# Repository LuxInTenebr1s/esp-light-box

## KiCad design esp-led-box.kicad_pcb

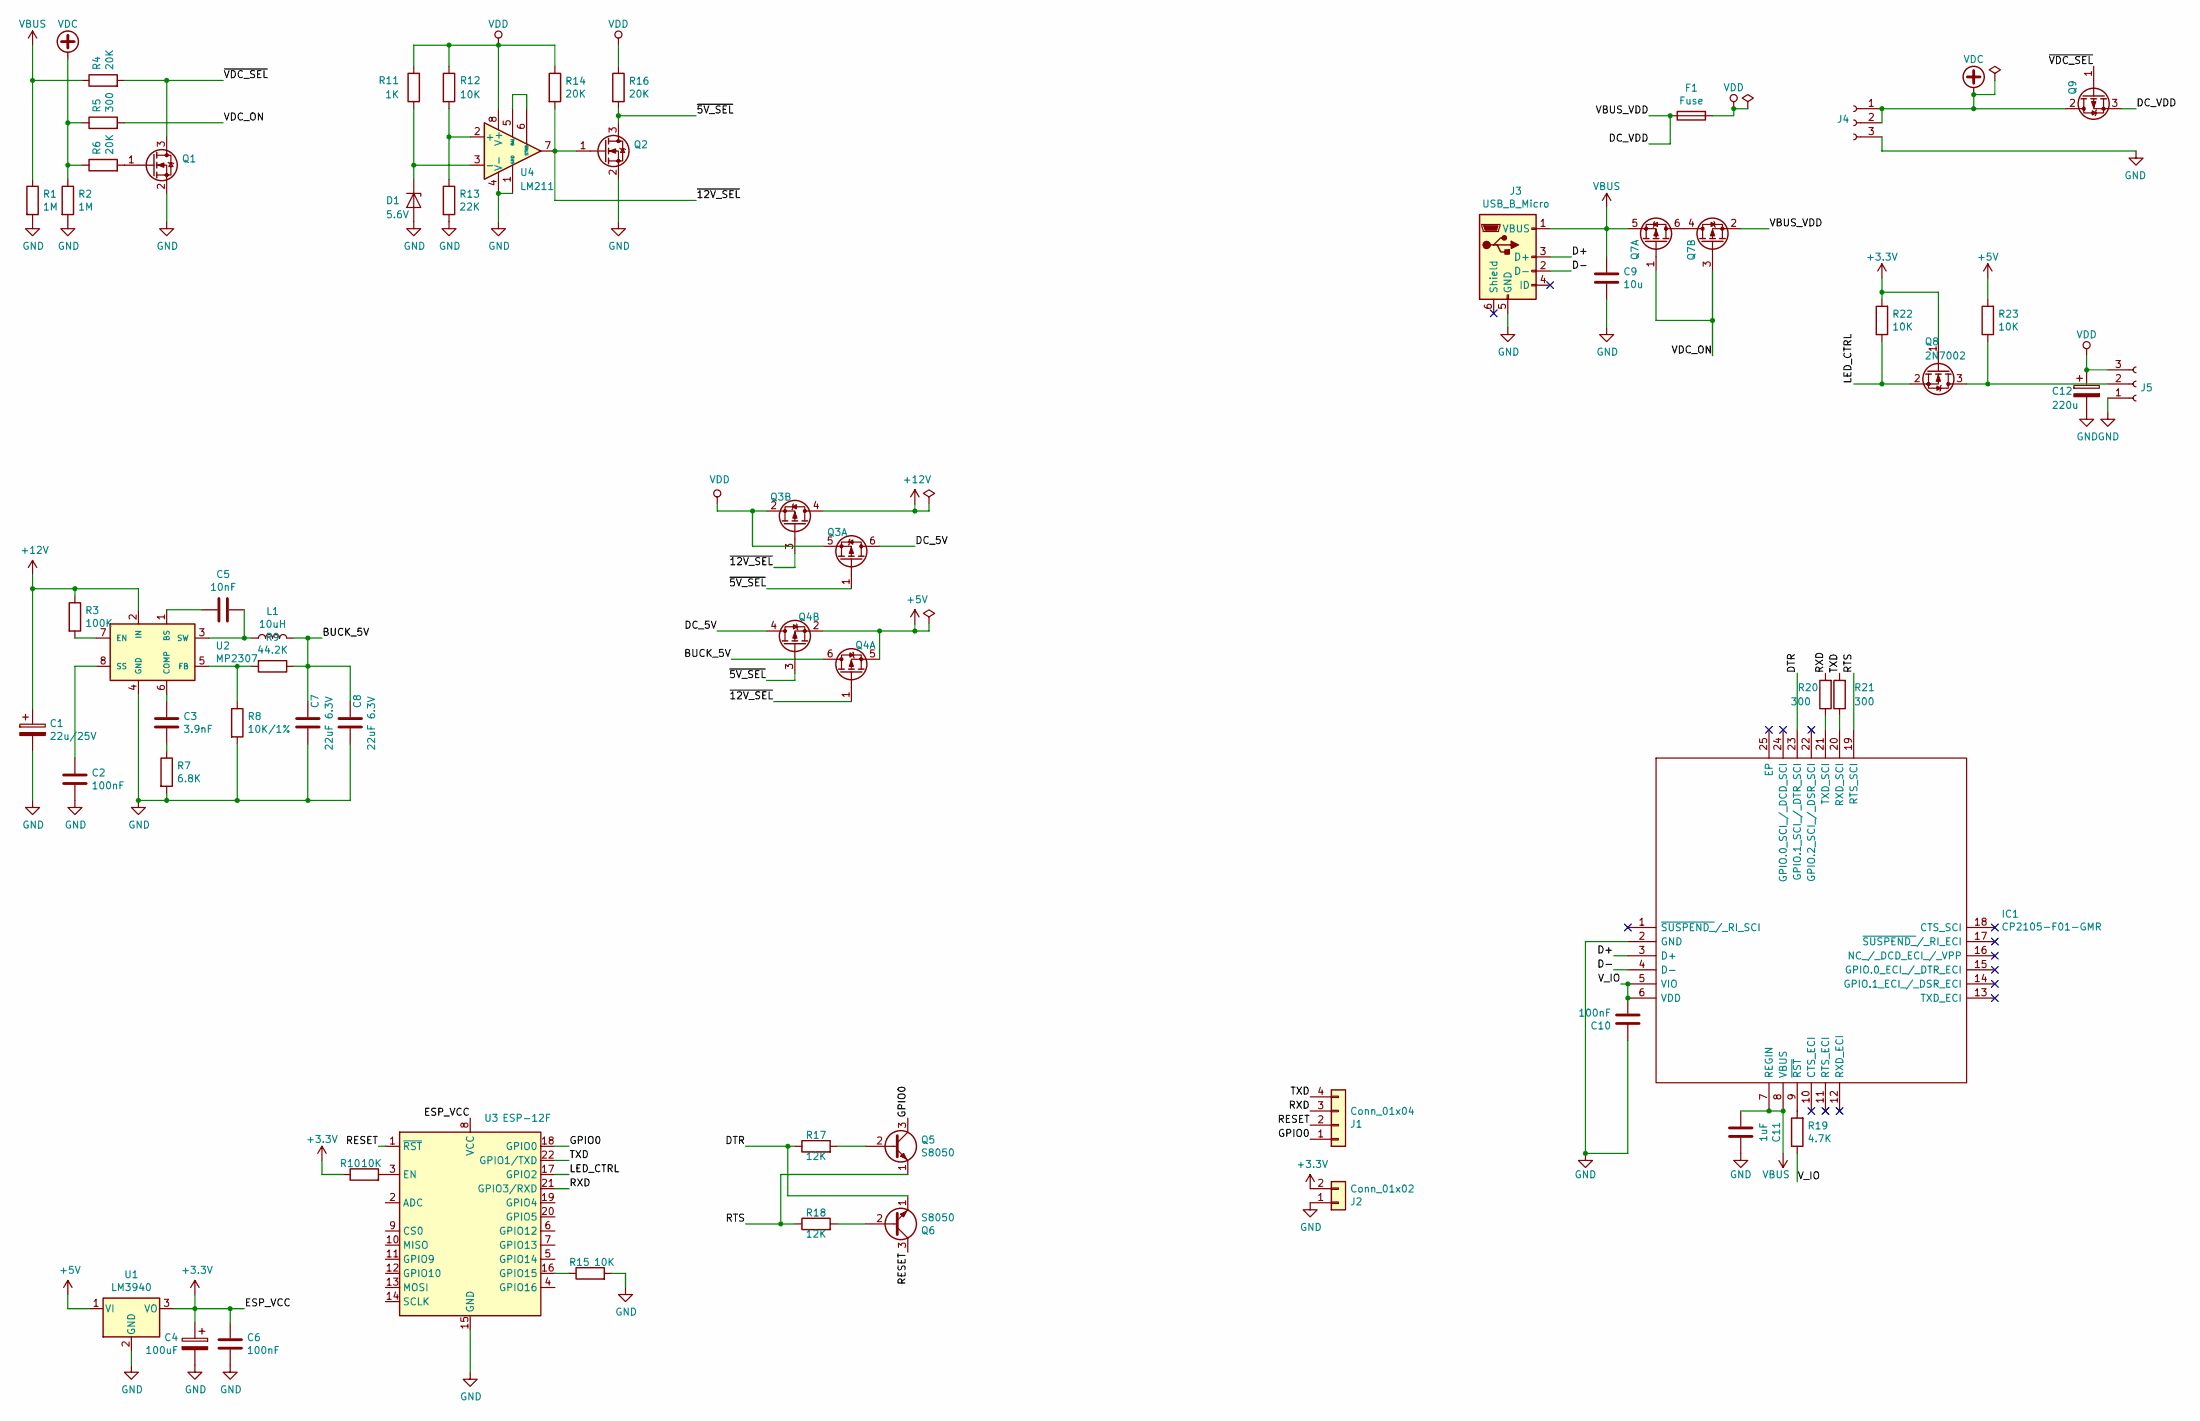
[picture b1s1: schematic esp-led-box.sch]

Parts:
C1: 22u/25V; C_0805_2012Metric; LCSC C45783
C2, C6, C10: 100nF; C_0402_1005Metric; LCSC C307331
C3: 3.9nF; C_0402_1005Metric; LCSC C18047
C4: 100uF; CP_EIA-3528-21_Kemet-B; LCSC C16133
C5: 10nF; C_0402_1005Metric; LCSC C15195
C7, C8: 22uF 6.3V; C_0603_1608Metric; LCSC C59461
C9: 10u; C_0603_1608Metric; LCSC C19702
C11: 1uF; C_0402_1005Metric
C12: 220u; CP_Elec_6.3x7.7; LCSC C127327
D1: 5.6V; D_MiniMELF; LCSC C8062
F1: Fuse; fuseholder_blade_common_aliexpress
IC1: CP2105-F01-GMR; QFN50P400X400X80-25N-D; Manufacturer_Part_Number CP2105-F01-GMR; Mouser Part Number 634-CP2105-F01-GMR
J1: Conn_01x04; PinHeader_1x04_P2.54mm_Vertical
J2: Conn_01x02; PinHeader_1x02_P2.54mm_Vertical
J3: USB_B_Micro; USB_Micro-B_Molex-105017-0001
J4, J5: Conn_01x03_Female; SolderWire_1x03_2.5x6
L1: 10uH; L_Sunlord_MWSA0518_5.4x5.2mm; LCSC C181721
Q1, Q2, Q8: 2N7002; SOT-23; LCSC C8545
Q3, Q4, Q7: Q_PMOS_DGS; SOT-23-6; LCSC C148368
Q5, Q6: S8050; SOT-23; LCSC C2146
Q9: Q_PMOS_DGS; TO-252-2; LCSC C67281
R1, R2: 1M; R_0402_1005Metric; LCSC C26083
R3: 100K; R_0402_1005Metric; LCSC C25741
R4, R6: 20K; R_0603_1608Metric; LCSC C4184
R5: 300; R_0805_2012Metric; LCSC C17617
R7: 6.8K; R_0402_1005Metric; LCSC C25917
R8: 10K/1%; R_0402_1005Metric; LCSC C25744
R9: 44.2K; R_0402_1005Metric; LCSC C25895
R10, R12, R15, R22, R23: 10K; R_0402_1005Metric; LCSC C25744
R11: 1K; R_0603_1608Metric; LCSC C21190
R13: 22K; R_0402_1005Metric; LCSC C25768
R14, R16: 20K; R_0402_1005Metric; LCSC C25765
R17, R18: 12K; R_0402_1005Metric; LCSC C25752
R19: 4.7K; R_0402_1005Metric; LCSC C25900
R20, R21: 300; R_0402_1005Metric; LCSC C25774
U1: LM3940; SOT-223-3_TabPin2; LCSC C140319
U2: MP2307; SOIC-8_3.9x4.9mm_P1.27mm; LCSC C18921
U3: ESP-12F; ESP-12E
U4: LM211; SOIC-8-1EP_3.9x4.9mm_P1.27mm_EP2.29x3mm; LCSC C99580

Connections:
+3V3: C4.1, C6.1, J2.2, Q8.1 (G), R10.1, R22.2, U1.3 (VO), U3.8 (VCC)
+5V: Q4.2 (S), Q4.5 (S), R23.2, U1.1 (VI)
+12V: C1.1, Q3.4 (D), R3.1, U2.2 (IN)
/BUCK_5V: C7.1, C8.1, L1.2, Q4.6 (D), R9.1
/D+: IC1.3 (D+), J3.3 (D+)
/D-: IC1.4 (D-), J3.2 (D-)
/DC_5V: Q3.6 (D), Q4.4 (D)
/DC_VDD: F1.1, Q7.2 (S), Q9.3 (S)
/DTR: IC1.23 (GPIO.1_SCI_/_DTR_SCI), Q6.1 (E), R17.1
/GPIO0: J1.1, Q5.3 (C), U3.18 (GPIO0)
/LED_CTRL: Q8.2 (S), R22.1, U3.17 (GPIO2)
/RESET: J1.2, Q6.3 (C), U3.1 (~RST)
/RTS: IC1.19 (RTS_SCI), Q5.1 (E), R18.1
/RXD: J1.3, R20.2, U3.21 (GPIO3/RXD)
/TXD: J1.4, R21.2, U3.22 (GPIO1/TXD)
/VDC_ON: Q7.1 (G), Q7.3 (G), R5.2
/V_IO: C10.2, IC1.5 (VIO), IC1.6 (VDD), R19.1
/~5V_SEL: Q2.3 (D), Q3.1 (G), Q4.3 (G), R16.2; also elsewhere on the board
/~12V_SEL: Q2.1 (G), Q3.3 (G), Q4.1 (G), R14.2, U4.7; also elsewhere on the board
/~VDC_SEL: Q1.3 (D), Q9.1 (G), R4.2
GND: C1.2, C2.2, C4.2, C6.2, C7.2, C8.2, C9.1, C10.1, C11.2, C12.2, D1.2 (A), IC1.2 (GND), J2.1, J3.5 (GND), J4.3, J5.1, Q1.2 (S), Q2.2 (S), R1.2, R2.2, R7.2, R8.2, R13.2, R15.2, U1.2 (GND), U2.4 (GND), U3.15 (GND), U4.1 (GND), U4.4 (V-); also elsewhere on the board
unnamed: C2.1, U2.8 (SS)
unnamed: C3.1, U2.6 (COMP)
unnamed: C3.2, R7.1
unnamed: C5.1, L1.1, U2.3 (SW)
unnamed: C5.2, U2.1 (BS)
unnamed: D1.1 (K), R11.1, U4.3 (-)
unnamed: IC1.9 (~RST), R19.2
unnamed: IC1.20 (RXD_SCI), R21.1
unnamed: IC1.21 (TXD_SCI), R20.1
unnamed: J5.2, Q8.3 (D), R23.1
unnamed: Q1.1 (G), R6.2
unnamed: Q5.2 (B), R17.2
unnamed: Q6.2 (B), R18.2
unnamed: Q7.4 (D), Q7.6 (D)
unnamed: R3.2, U2.7 (EN)
unnamed: R8.1, R9.2, U2.5 (FB)
unnamed: R10.2, U3.3 (EN)
unnamed: R12.2, R13.1, U4.2 (+)
unnamed: R15.1, U3.16 (GPIO15)
unnamed: U4.5 (BAL), U4.6 (STRB)
VBUS: C9.2, C11.1, IC1.7 (REGIN), IC1.8 (VBUS), J3.1 (VBUS), Q7.5 (S), R1.1, R4.1
VDC: J4.1, J4.2, Q9.2 (D), R2.1, R5.1, R6.1
VDD: C12.1, F1.2, J5.3, Q3.2 (S), Q3.5 (S), R11.2, R12.1, R14.1, R16.1, U4.8 (V+)

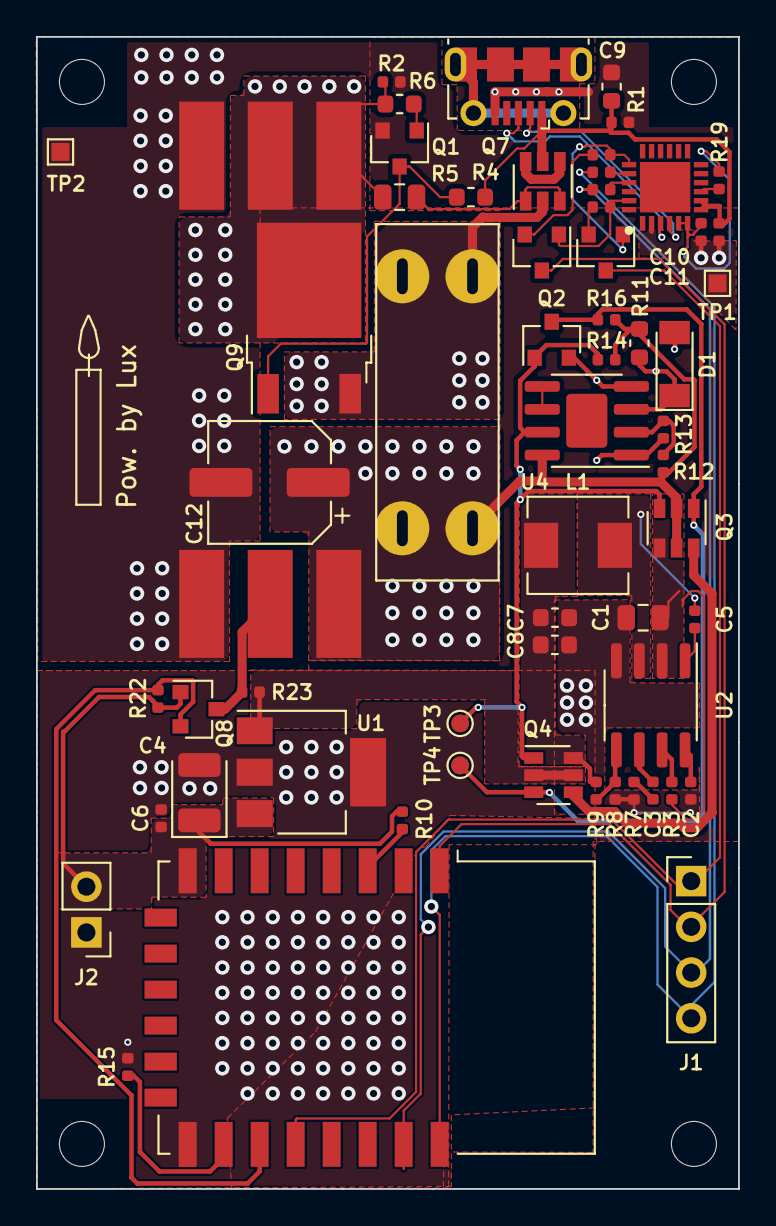
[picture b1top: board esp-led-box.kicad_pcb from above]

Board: 2 copper layers, 39.0 x 64.0 mm, 61 parts (0 on the bottom side), 44 nets.

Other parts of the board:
TP1, TP2: GND; TestPoint_Pad_1.0x1.0mm
TP3: ~12V_SEL; TestPoint_Pad_D1.0mm
TP4: ~5V_SEL; TestPoint_Pad_D1.0mm

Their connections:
/~5V_SEL: TP4.1; also elsewhere on the board
/~12V_SEL: TP3.1; also elsewhere on the board
GND: TP1.1, TP2.1; also elsewhere on the board

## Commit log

2020-03-11 git: add .gitignore file
2020-03-13 Fixed iteration #2
    - replace 0603 SMDs with 1206 ones;
    - add fuse holder
    - add two ACT LEDs
    - fix level shifter transistor scheme
    - add degson terminal block
    - use 2.56 pin header
2020-03-19 pcb: make ready for manufacturing
    - dummy resistors to switch from +12v power input to +5v input to make box be usable with different LED strips
    - some cosmetic changes withing .sch
    - put protection diode inline not parallel
2020-03-19 silkmask: fix designators overlap
2020-03-22 rework fuse holder: use one from aliexpress
    https://aliexpress.ru/item/32838425418.html?spm=a2g0s.9042311.0.0.5f9933edQqCEM1 here is the link (it supposed to be used with micro blades fuses)
2020-10-11 pcb v0.3 update
    - add possibility to use switch instead of dummy resisters
    - add micro USB footprint for portable use
    - add buttons for RESET and GPIO0 ESP inputs
    - make it fancier with components density increased
    - add case mountpoints
2021-06-15 pre-version: still needs to fix some problems and breadboard it
2021-07-16 my new version is coming
2021-07-16 kek forgot it
2021-07-16 another kek
2021-07-16 another kek hehe
2021-07-17 will I ever stop?
2021-07-17 finally we are done
2021-07-17 ... dont say anything
